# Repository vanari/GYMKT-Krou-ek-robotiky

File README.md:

# GYMKT-Krouzek-robotiky 
## Robot na robotickou soutěž Plzeňského kraje
## robot-5.1.ino - soubory s programem
## documentation - dokumentace robota v pdf

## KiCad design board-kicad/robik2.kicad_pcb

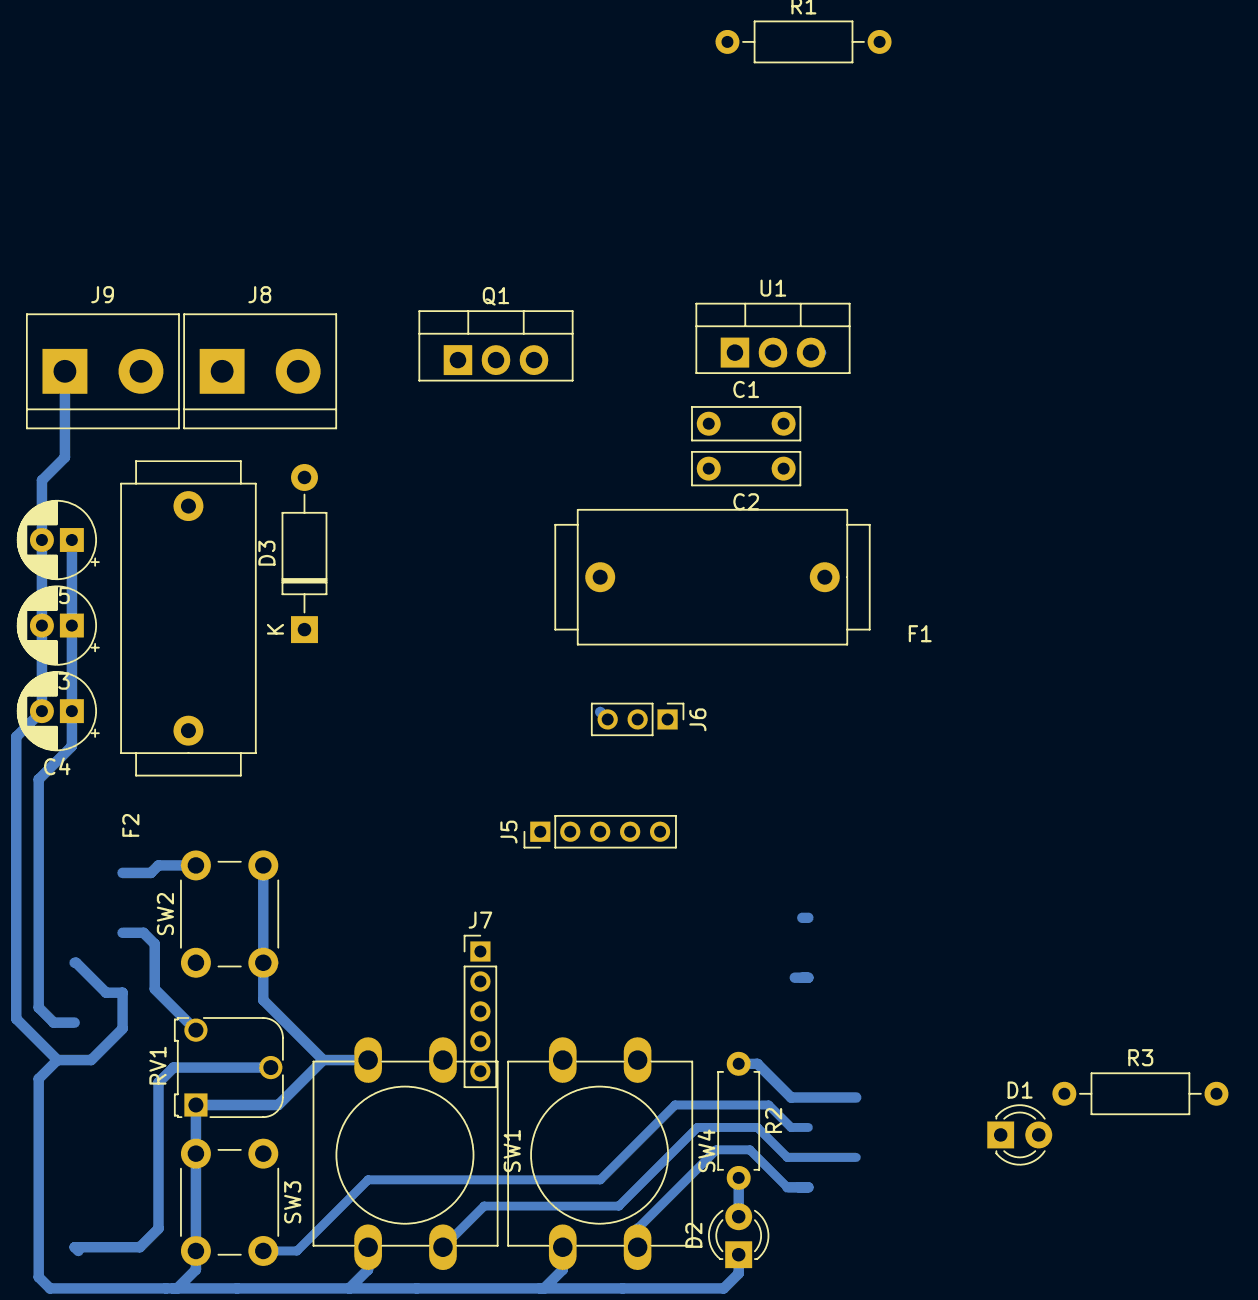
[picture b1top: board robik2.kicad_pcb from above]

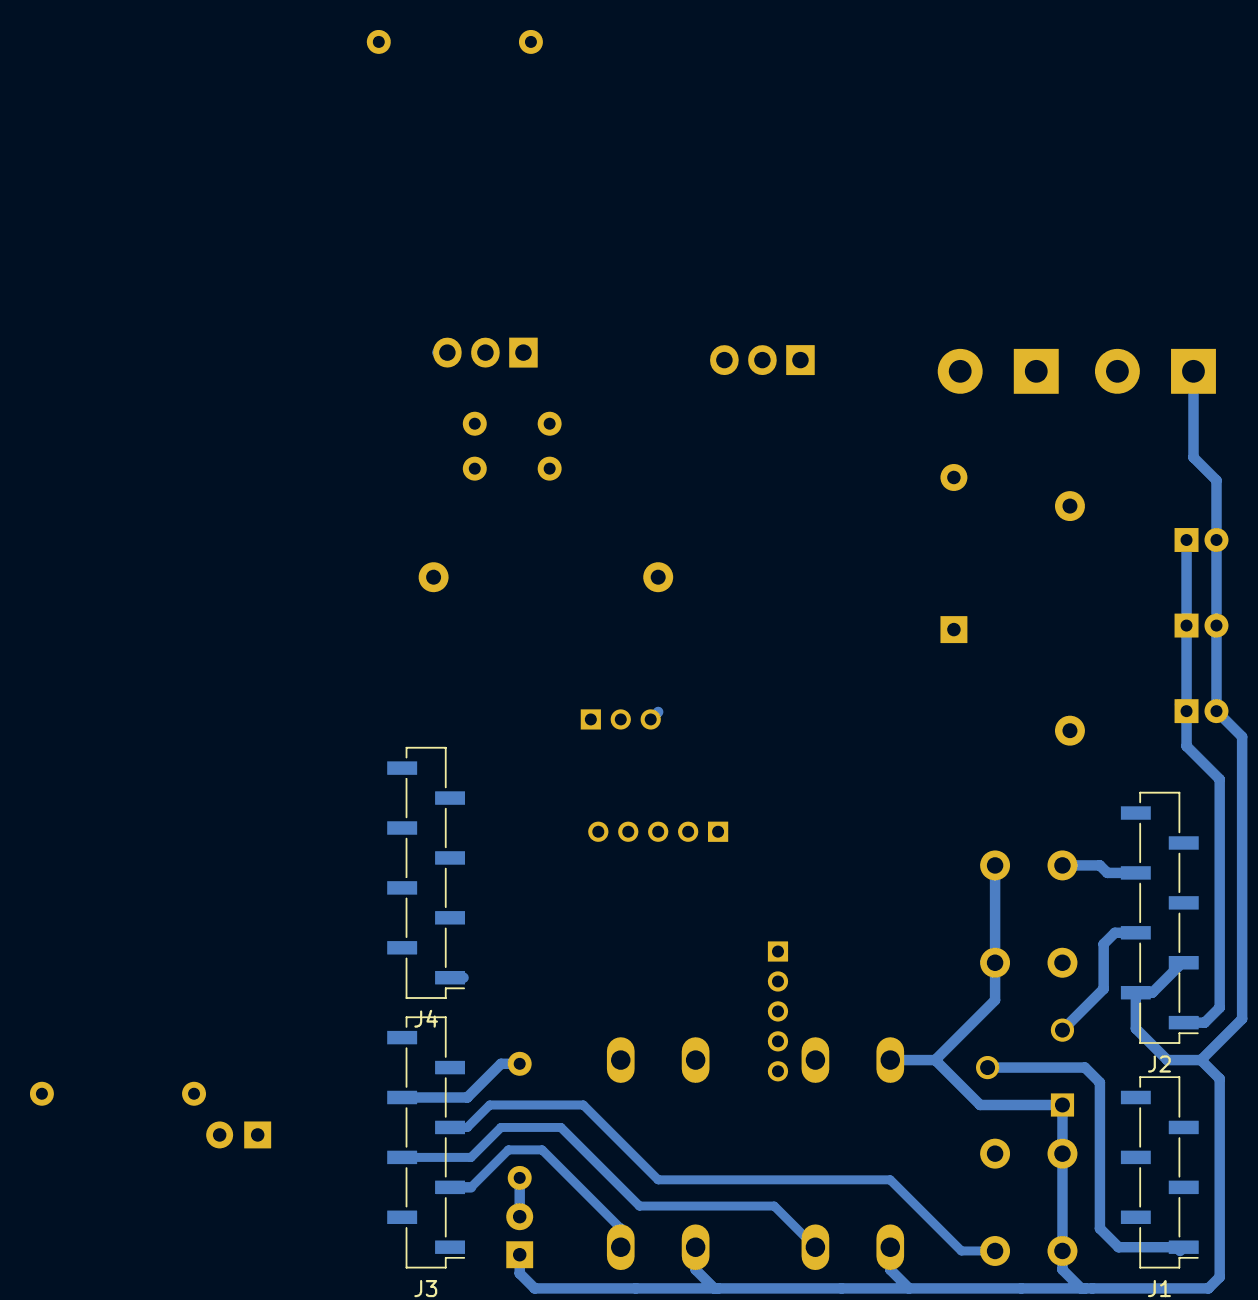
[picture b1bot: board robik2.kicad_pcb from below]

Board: 2 copper layers, 29 parts (4 on the bottom side), 21 nets.

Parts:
C1, C2: C; C_Rect_L7.0mm_W2.0mm_P5.00mm
C3, C4, C5: CP; CP_Radial_D5.0mm_P2.00mm
D1, D2: LED; LED_D3.0mm
D3: 1N4007; D_A-405_P10.16mm_Horizontal
F1: Pojistka 1A; Fuse_sbeve
F2: Pojistka 2A; Fuse_sbeve
J1: Analog 0-5; PinSocket_1x06_P2.00mm_Vertical_SMD_Pin1Left
J2: Power and other; PinSocket_1x08_P2.00mm_Vertical_SMD_Pin1Left
J3: Digital 0-7; PinSocket_1x08_P2.00mm_Vertical_SMD_Pin1Left
J4: Digital 8-13; PinSocket_1x08_P2.00mm_Vertical_SMD_Pin1Left
J5: Ultrasound 1; PinHeader_1x05_P2.00mm_Vertical
J6: Servo; PinHeader_1x03_P2.00mm_Vertical
J7: Ultrasound 2; PinHeader_1x05_P2.00mm_Vertical
J8: Motor terminal; TerminalBlock_bornier-2_P5.08mm
J9: Battery terminal; TerminalBlock_bornier-2_P5.08mm
Q1: BUZ11; TO-220-3_Vertical
R1, R3: R; R_Axial_DIN0207_L6.3mm_D2.5mm_P10.16mm_Horizontal
R2: R; R_Axial_DIN0207_L6.3mm_D2.5mm_P7.62mm_Horizontal
RV1: R_POT_TRIM; Potentiometer_Runtron_RM-065_Vertical
SW1: Greenbtn; SW_PUSH-12mm
SW2: Resetbtn; SW_PUSH_6mm
SW3: Ebtn; SW_PUSH_6mm
SW4: Redbtn; SW_PUSH-12mm
U1: LM7805_TO220; TO-220-3_Vertical

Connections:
+5V: C2.1, F1.1, U1.3
+5VA: J2.4, J5.5, J7.5, R3.1, RV1.3
+7.5V: C1.1, C3.1, C4.1, C5.1, D3.1, F2.1, J2.1, J8.1, U1.1
GND: C1.2, C2.2, C3.2, C4.2, C5.2, D1.1, D2.1, J2.2, J2.3, J5.1, J6.1, J7.1, J9.1, Q1.3, R1.2, RV1.1, SW1.2, SW2.2, SW3.2, SW4.2, U1.2
unnamed: D1.2, R3.2
unnamed: D2.2, R2.2
unnamed: D3.2, J8.2, Q1.2
unnamed: F1.2, J6.3
unnamed: F2.2, J9.2
unnamed: J1.1, RV1.2
unnamed: J2.6, SW2.1
unnamed: J3.3, SW4.1
unnamed: J3.4, SW1.1
unnamed: J3.5, SW3.1
unnamed: J3.6, R2.1
unnamed: J3.7, J5.4
unnamed: J3.8, J5.3
unnamed: J4.1, J7.4
unnamed: J4.2, J7.3
unnamed: J4.3, J6.2
unnamed: J4.4, Q1.1, R1.1

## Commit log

2020-08-13 added eagle
2020-09-04 added schematics
2020-09-24 board
2020-10-08 added whole bunch of stuff
2021-08-23 updated robot
2021-08-29 cocc
